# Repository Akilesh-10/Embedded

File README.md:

# Embedded

## Cadlab link for Wireless Temperature Sensor
https://cadlab.io/project/29082/main/files

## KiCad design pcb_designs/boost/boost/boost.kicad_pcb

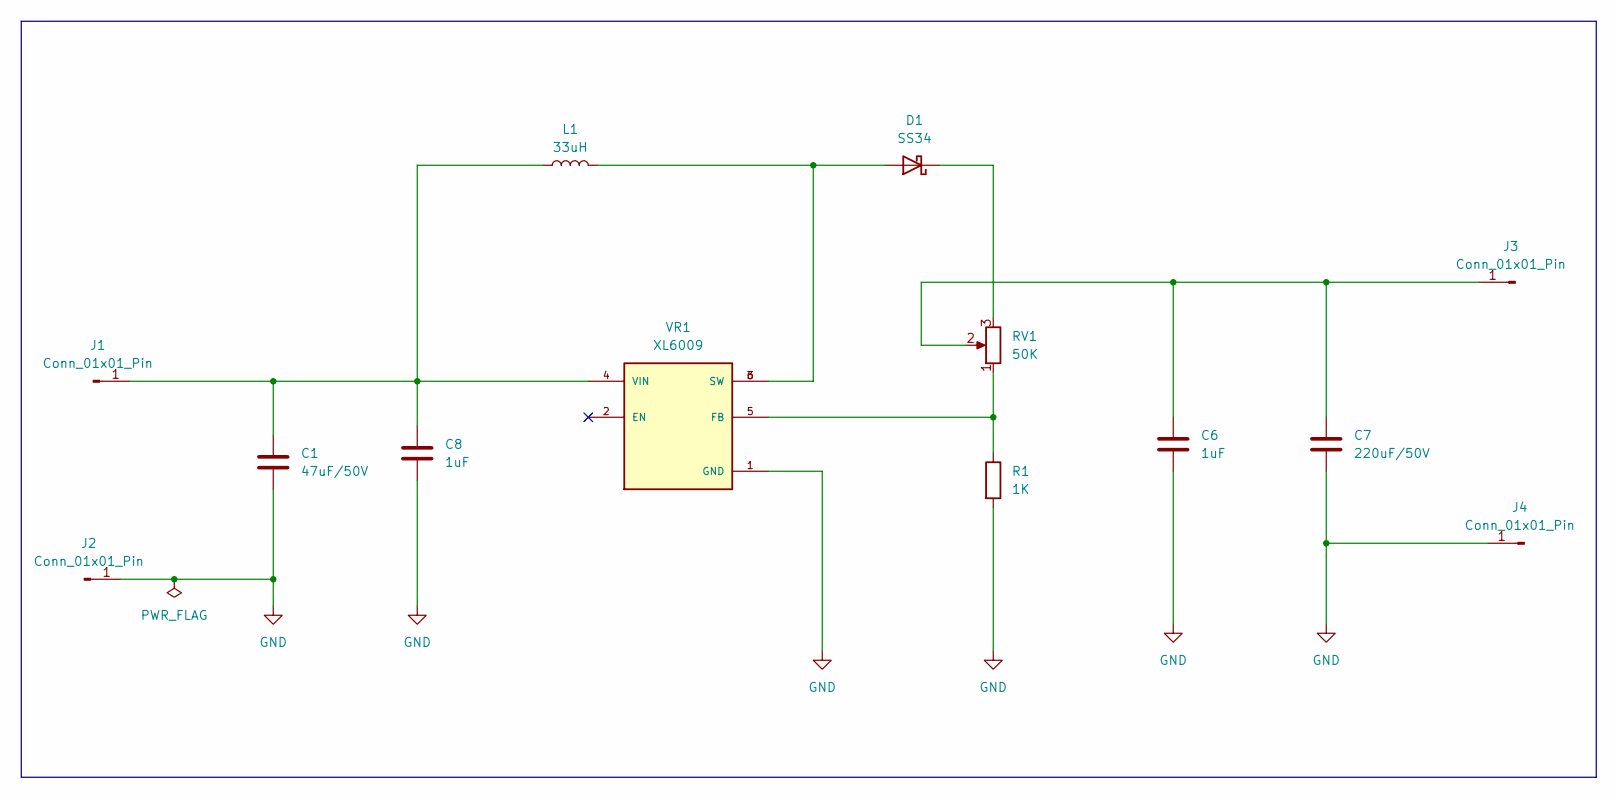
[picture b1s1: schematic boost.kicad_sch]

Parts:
C1: 47uF/50V; C_Radial_D8.0mm_H7.0mm_P3.50mm
C6, C8: 1uF; C_0805_2012Metric
C7: 220uF/50V; C_Radial_D8.0mm_H7.0mm_P3.50mm
D1: SS34; D_SMA
J1, J2, J3, J4: Conn_01x01_Pin; PinHeader_1x01_P2.54mm_Vertical
L1: 33uH; L_12x12mm_H8mm
R1: 1K; R_1206_3216Metric
RV1: 50K; Potentiometer_Bourns_3296Y_Vertical
VR1: XL6009; DPAK170P1435X465-6N; PARTREV 1.1

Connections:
GND: C1.2, C6.2, C7.2, C8.2, J2.1, J4.1, R1.2, VR1.1 (GND)
unnamed: D1.2 (A), L1.2, VR1.3 (SW), VR1.6 (SW)
unnamed: D1.1 (K), RV1.3
unnamed: C1.1, C8.1, J1.1, L1.1, VR1.4 (VIN)
unnamed: C6.1, C7.1, J3.1, RV1.2
unnamed: R1.1, RV1.1, VR1.5 (FB)

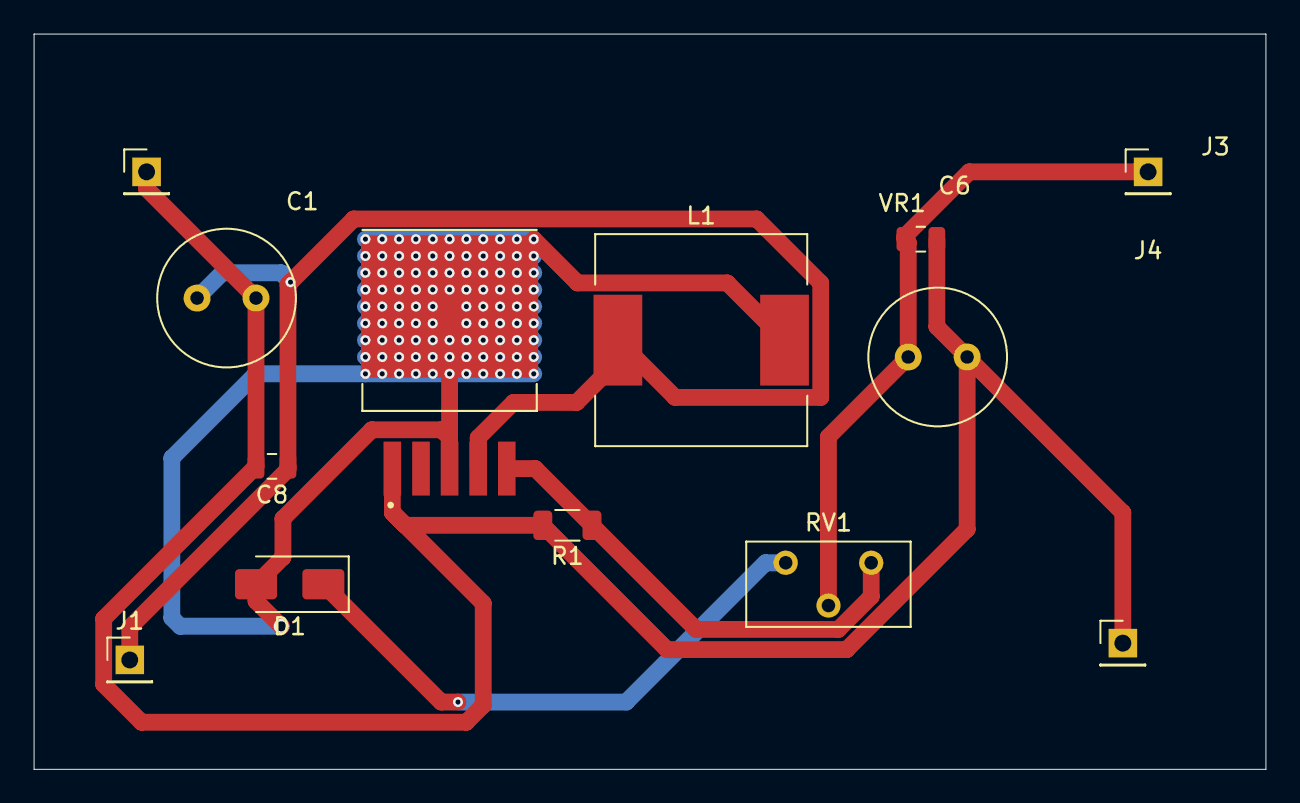
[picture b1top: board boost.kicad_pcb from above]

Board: 2 copper layers, 73.2 x 43.7 mm, 13 parts (0 on the bottom side), 6 nets.

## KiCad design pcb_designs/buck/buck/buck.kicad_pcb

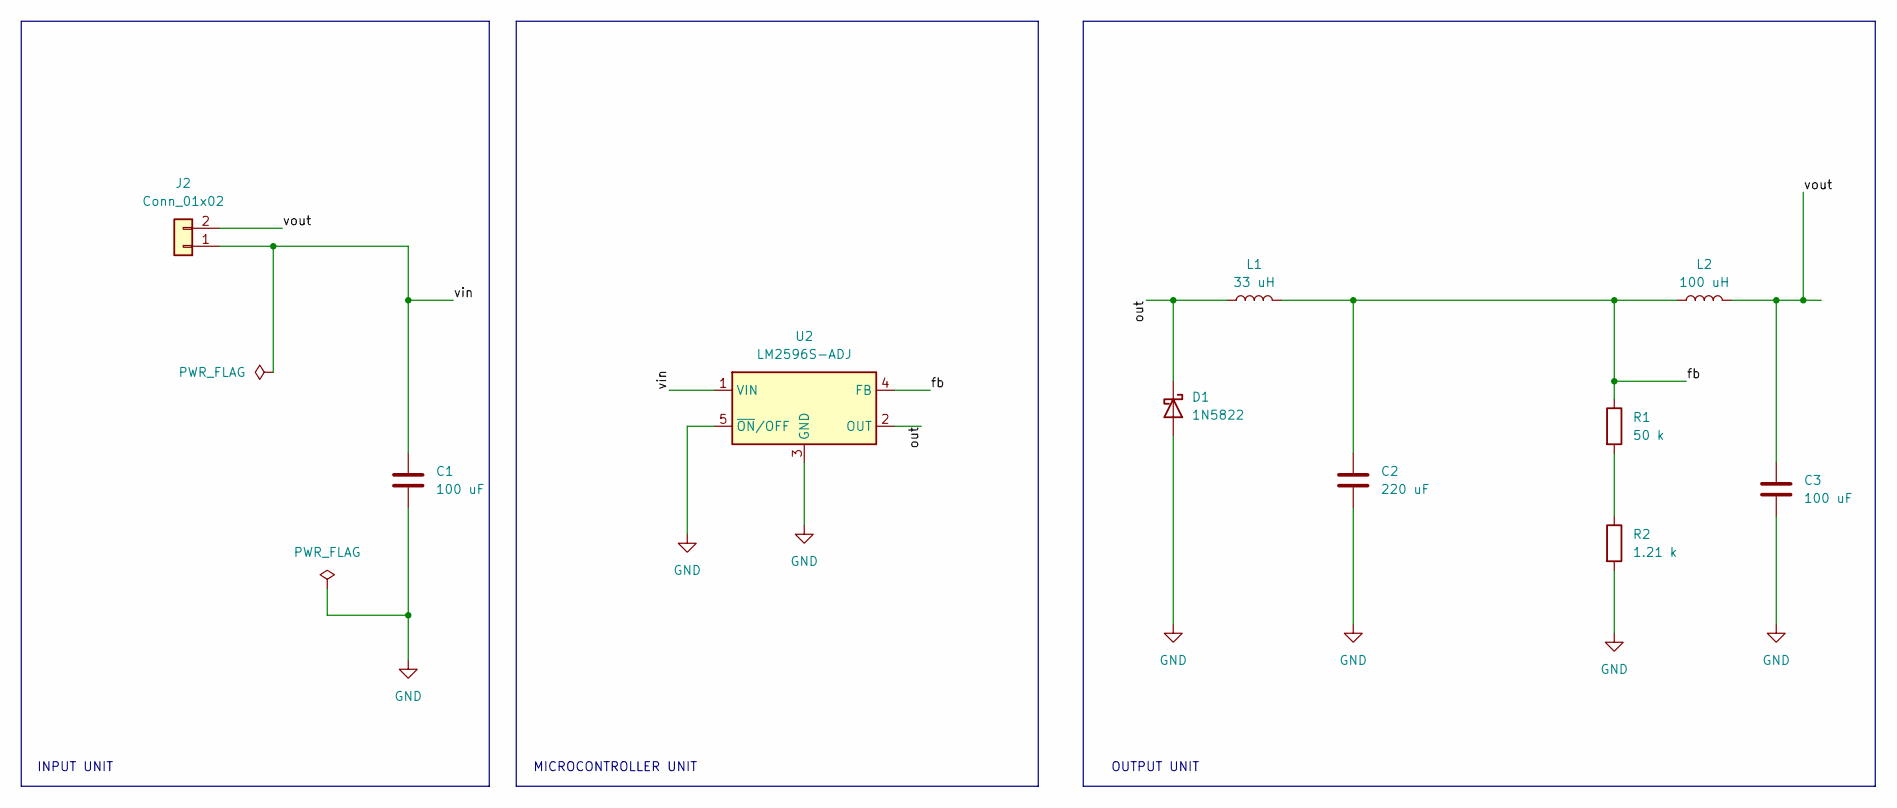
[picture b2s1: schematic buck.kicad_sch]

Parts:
C1, C3: 100 uF; C_Radial_D8.0mm_H7.0mm_P3.50mm
C2: 220 uF; C_Radial_D8.0mm_H7.0mm_P3.50mm
D1: 1N5822; D_DO-201AD_P15.24mm_Horizontal
J2: Conn_01x02; SolderWire-2.5sqmm_1x02_P7.2mm_D2.4mm_OD3.6mm
L1: 33 uH; L_Radial_D10.0mm_P5.00mm_Fastron_07M
L2: 100 uH; L_Radial_D10.0mm_P5.00mm_Fastron_07M
R1: 50 k; R_Axial_DIN0207_L6.3mm_D2.5mm_P7.62mm_Horizontal
R2: 1.21 k; R_Axial_DIN0207_L6.3mm_D2.5mm_P7.62mm_Horizontal
U2: LM2596S-ADJ; TO-263-5_TabPin3

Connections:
/fb: C2.1, L1.2, L2.1, R1.1, U2.4 (FB)
/out: D1.1 (K), L1.1, U2.2 (OUT)
/vin: C1.1, J2.1, U2.1 (VIN)
/vout: C3.1, J2.2, L2.2
GND: C1.2, C2.2, C3.2, D1.2 (A), R2.2, U2.3 (GND), U2.5 (~ON/OFF)
unnamed: R1.2, R2.1

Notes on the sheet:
MICROCONTROLLER UNIT
INPUT UNIT
OUTPUT UNIT

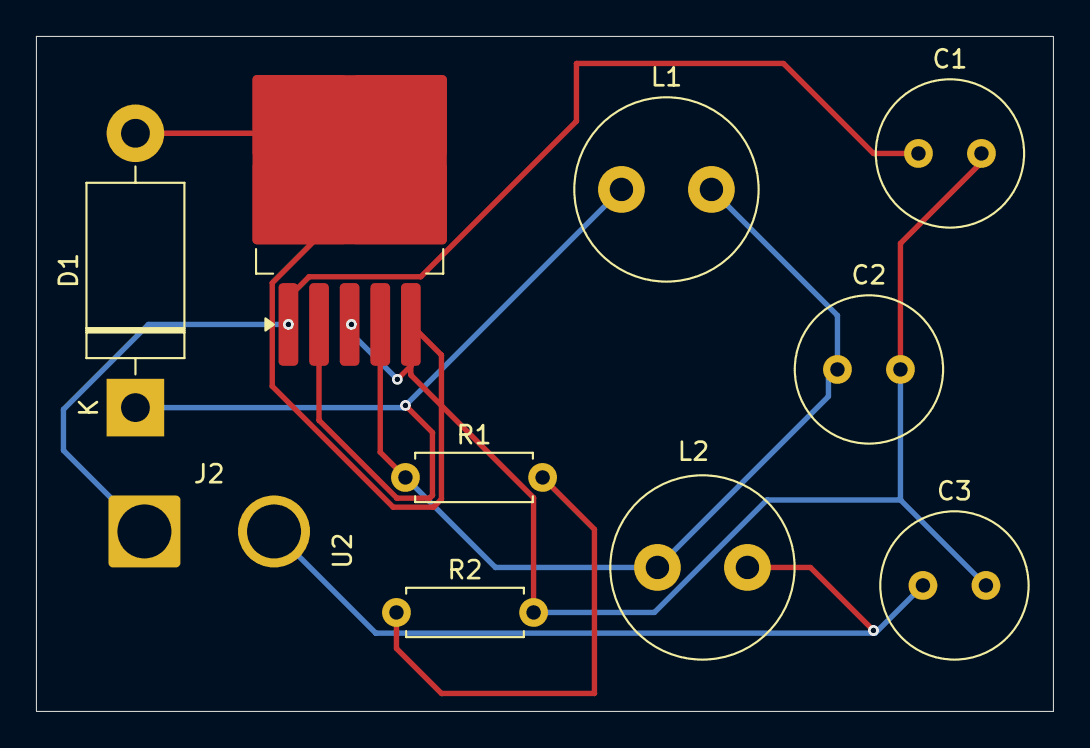
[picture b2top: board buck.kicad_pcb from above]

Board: 2 copper layers, 56.5 x 37.5 mm, 10 parts (0 on the bottom side), 6 nets.

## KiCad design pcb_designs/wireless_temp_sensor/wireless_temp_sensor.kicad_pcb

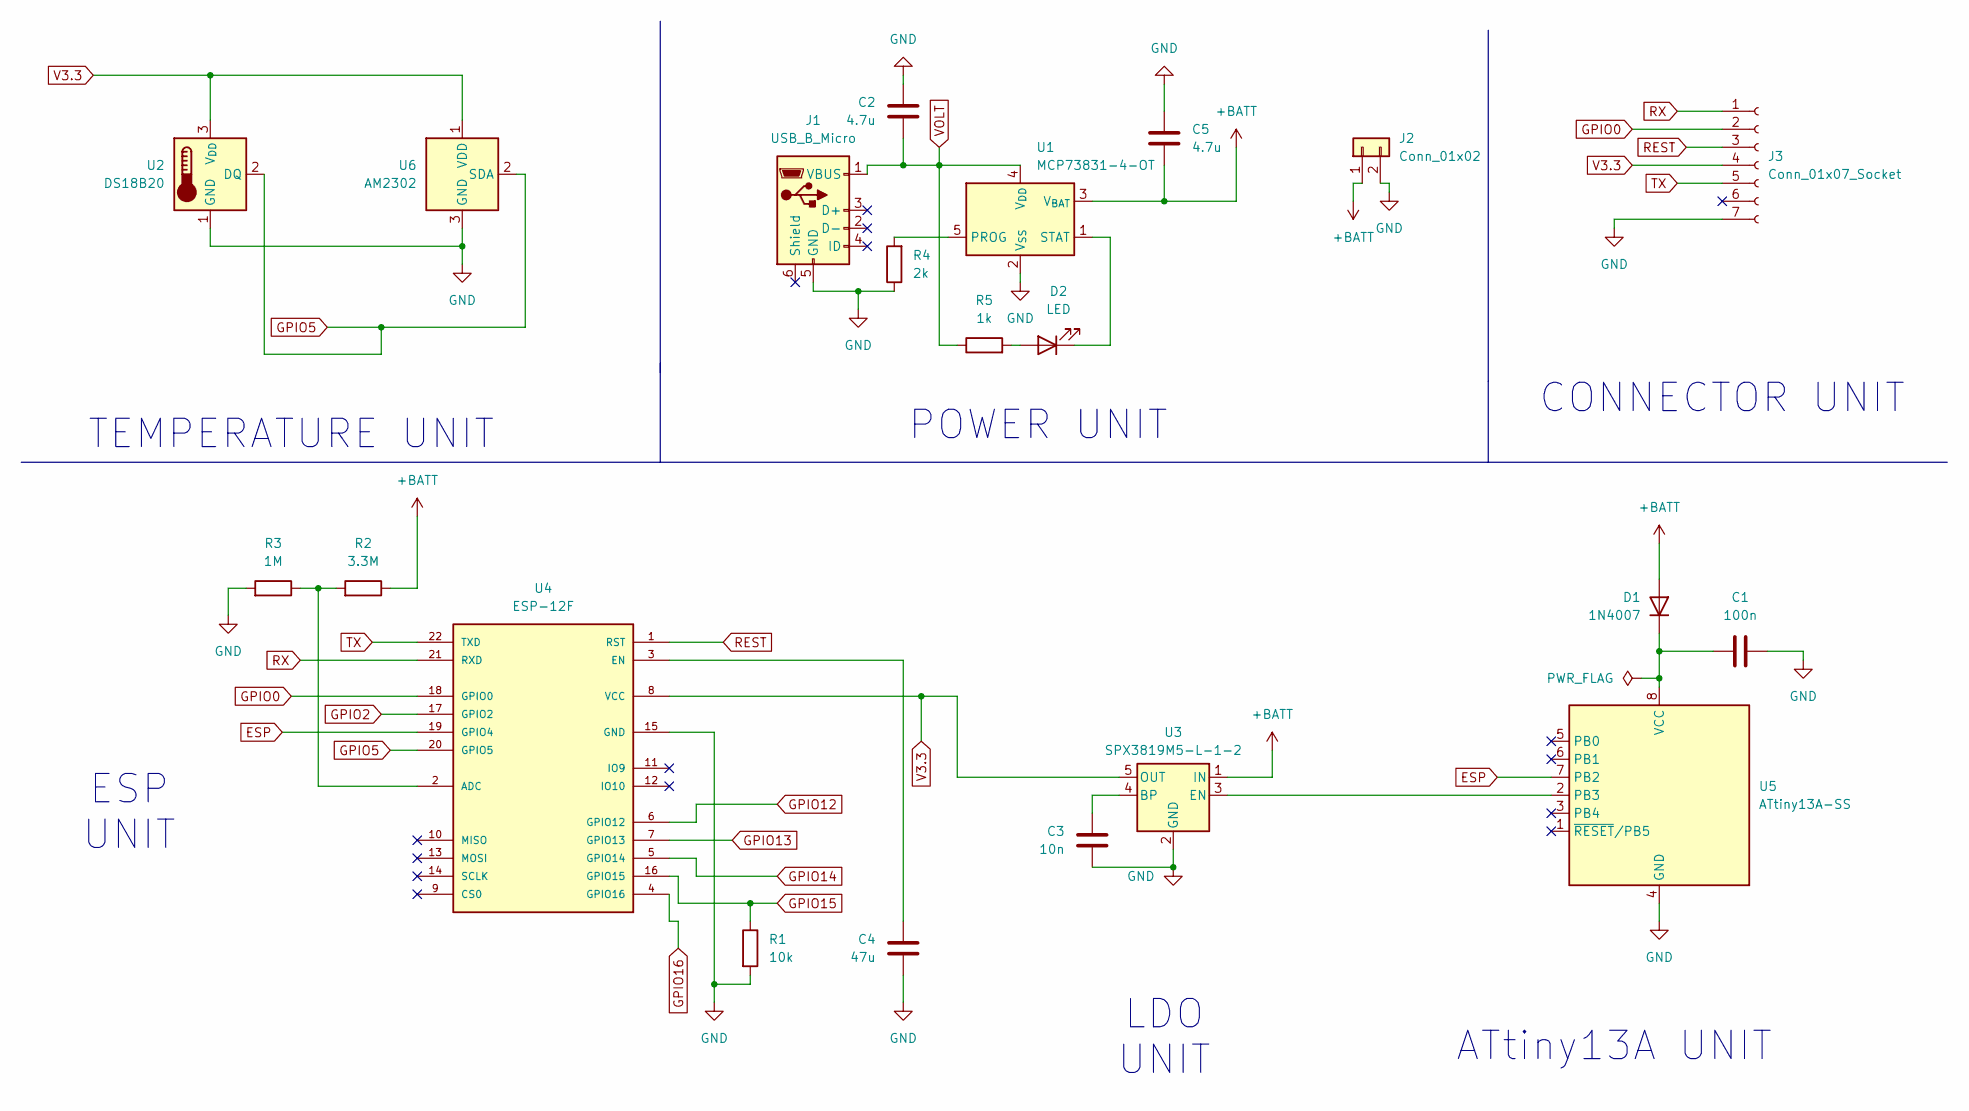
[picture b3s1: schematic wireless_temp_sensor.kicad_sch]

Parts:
C1: 100n; C_0603_1608Metric
C2, C5: 4.7u; C_1206_3216Metric
C3: 10n; C_0603_1608Metric
C4: 47u; C_1812_4532Metric
D1: 1N4007; D_DO-41_SOD81_P10.16mm_Horizontal
D2: LED; LED_0603_1608Metric
J1: USB_B_Micro; USB_Micro-B_GCT_USB3076-30-A
J2: Conn_01x02; PinHeader_1x02_P2.54mm_Horizontal
J3: Conn_01x07_Socket; PinHeader_1x07_P2.54mm_Vertical
R1: 10k; R_0603_1608Metric
R2: 3.3M; R_0603_1608Metric
R3: 1M; R_0603_1608Metric
R4: 2k; R_0603_1608Metric
R5: 1k; R_0603_1608Metric
U1: MCP73831-4-OT; SOT-23-5
U2: DS18B20; TO-92_Inline
U3: SPX3819M5-L-1-2; SOT-23-5
U4: ESP-12F
U5: ATtiny13A-SS; SOIC-8_3.9x4.9mm_P1.27mm
U6: AM2302; ASAIR_AM2302_P2.54mm_Vertical

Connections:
+BATT: C5.2, D1.2 (A), J2.1, R2.1, U1.3 (V_{BAT}), U3.1 (IN)
ESP: U4.19 (GPIO4), U5.7 (PB2)
GND: C1.1, C2.2, C3.2, C4.2, C5.1, J1.5 (GND), J2.2, J3.7, R1.2, R3.2, R4.1, U1.2 (V_{SS}), U2.1 (GND), U3.2 (GND), U4.15 (GND), U5.4 (GND), U6.3 (GND), U6.4 (GND)
GPIO0: J3.2, U4.18 (GPIO0)
GPIO2: U4.17 (GPIO2)
GPIO5: U2.2 (DQ), U4.20 (GPIO5), U6.2 (SDA)
GPIO12: U4.6 (GPIO12)
GPIO13: U4.7 (GPIO13)
GPIO14: U4.5 (GPIO14)
GPIO15: R1.1, U4.16 (GPIO15)
GPIO16: U4.4 (GPIO16)
unnamed: C1.2, D1.1 (K), U5.8 (VCC)
unnamed: D2.2 (A), R5.2
unnamed: D2.1 (K), U1.1 (STAT)
unnamed: R4.2, U1.5 (PROG)
unnamed: C3.1, U3.4 (BP)
unnamed: U3.3 (EN), U5.2 (PB3)
unnamed: R2.2, R3.1, U4.2 (ADC)
unnamed: C4.1, U4.3 (EN)
REST: J3.3, U4.1 (RST)
RX: J3.1, U4.21 (RXD)
TX: J3.5, U4.22 (TXD)
V3.3: J3.4, U2.3 (V_{DD}), U3.5 (OUT), U4.8 (VCC), U6.1 (VDD)
VOLT: C2.1, J1.1 (VBUS), R5.1, U1.4 (V_{DD})

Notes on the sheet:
LDO UNIT
ATtiny13A UNIT
ESP UNIT
CONNECTOR UNIT
POWER UNIT
TEMPERATURE UNIT

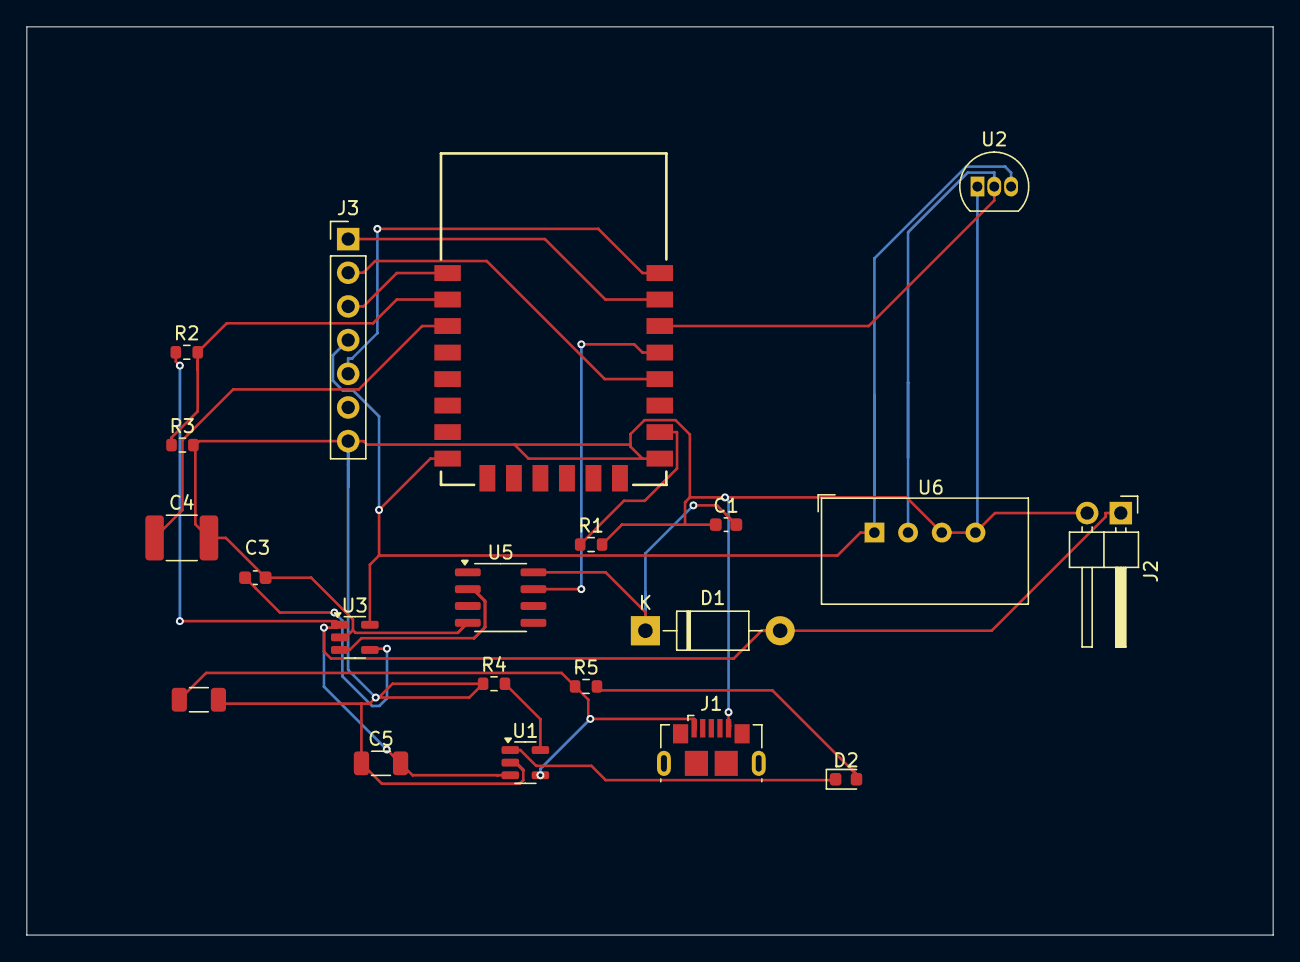
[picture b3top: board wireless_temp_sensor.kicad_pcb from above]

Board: 2 copper layers, 94.0 x 68.5 mm, 21 parts (0 on the bottom side), 19 nets.

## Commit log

2025-04-16 embedded
